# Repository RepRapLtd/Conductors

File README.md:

# Conductors
Experiments with 3D printing conducting filament

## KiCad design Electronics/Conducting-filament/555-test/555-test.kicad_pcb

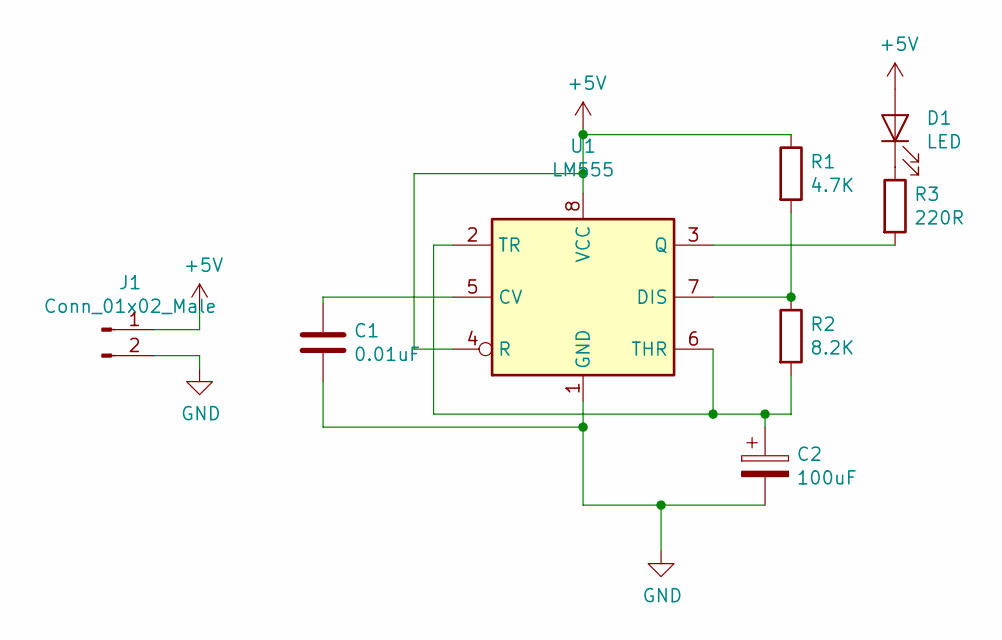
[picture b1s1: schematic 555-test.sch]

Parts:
C1: 0.01uF; C_Disc_D6.0mm_W2.5mm_P5.00mm
C2: 100uF; CP_Radial_D5.0mm_P2.50mm
D1: LED; LED_D3.0mm
J1: Conn_01x02_Male; PinHeader_1x02_P2.54mm_Vertical
R1: 4.7K; R_Axial_DIN0207_L6.3mm_D2.5mm_P7.62mm_Horizontal
R2: 8.2K; R_Axial_DIN0207_L6.3mm_D2.5mm_P7.62mm_Horizontal
R3: 220R; R_Axial_DIN0207_L6.3mm_D2.5mm_P7.62mm_Horizontal
U1: LM555; DIP-8_W7.62mm

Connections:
+5V: D1.2 (A), J1.1, R1.1, U1.4 (R), U1.8 (VCC)
GND: C1.2, C2.2, J1.2, U1.1 (GND)
unnamed: C1.1, U1.5 (CV)
unnamed: C2.1, R2.2, U1.2 (TR), U1.6 (THR)
unnamed: D1.1 (K), R3.1
unnamed: R1.2, R2.1, U1.7 (DIS)
unnamed: R3.2, U1.3 (Q)

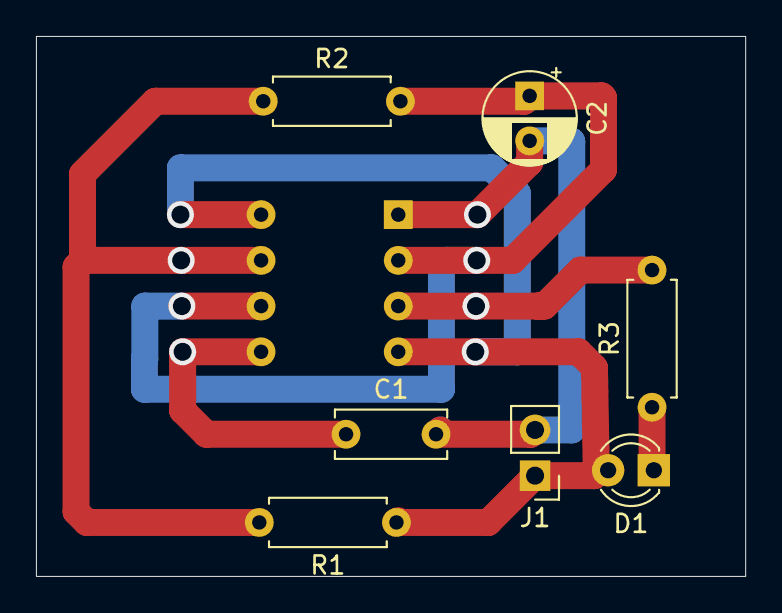
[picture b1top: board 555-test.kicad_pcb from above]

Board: 2 copper layers, 39.4 x 30.0 mm, 8 parts (1 on the bottom side), 7 nets.

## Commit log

2022-07-16 FreeCAD Python program to create FFF printable electronics.
2022-07-19 Test print of chip holder.
2022-07-20 Further work on the Python track creating program.
2022-07-21 First attempt (not wholly successful) at laying down multiple tracks...
2022-07-25 Further work on test circuit.
2024-05-29 Bringing up to date.
2024-05-29 Updating
